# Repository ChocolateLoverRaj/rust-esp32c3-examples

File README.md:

# Programming ESP32-C3 with Rust
Examples with wiring diagrams for using some sensors with ESP32-C3, programmed with Rust

## Materials Needed
- ESP32-C3 (I bought [this one from AliExpress](https://www.aliexpress.us/item/3256805941172619.html), and I recommend buying it from "TENSTAR ROBOT")
- USB Cable to connect the ESP32-C3 to your computer. You can use a USB-A to USB-C cable or a USB-C to USB-C cable, they both work.
- Project-specific materials

## Try out the code
- Clone this repo
- Install Rust
- You may need to install some Rust stuff for ESP32-C3
- Plug in your ESP32-C3
- Make sure you have the permissions to access ESP32-C3 (`/dev/ttyACM0`)
- `cd` to the directory you want to run
- `cargo run`

## Supported Chips / Boards
This was originally only for the ESP32-C3, but it should be really easy to add support for other ESP32 chips / boards. Some examples already have support for the ESP32-S3 in addition to the C3, and there is one example for STM32, but it should be really easy to add support for other ESP32 chips / boards. Some examples already have support for the ESP32-S3 in addition to the C3, and there is one example for STM32. If you would like an example for a specific chip / board to be added, let me know. I have a ESP32-C3, ESP32-S3, and a stm32f103c8.

## `std` vs `no_std`
On ESP32 chips you can use Rust with `std` or `no_std`. Originally, every project in this repo used `std`. At some point I switched to using `no_std`. I don't recommend using `std` anymore. The old examples still use `std`. If you would like a `no_std` version of an example that is currently `std` only, let me know.

## On-demand Maintanance Mode
I want to maintain this repo to help people do stuff with their ESP32s. However, not all examples will be up to date. If there is an example that uses an out-of-date `esp-hal` version, is not working, or not working on your chip, or if you have a question, don't hesistate to create an issue. 

## Resources
This project is based off of these resources

### Rust on ESP32-C3
- [The Rust on ESP Book](https://docs.espressif.com/projects/rust/book/)
- [Embedded Rust (no_std) on Espressif](https://docs.espressif.com/projects/rust/no_std-training/)
- https://github.com/ivmarkov/rust-esp32-std-demo
- https://github.com/shanemmattner/ESP32-C3_Rust_Tutorials

### Project-specific resources
Can be found in the `README.md` files in folders

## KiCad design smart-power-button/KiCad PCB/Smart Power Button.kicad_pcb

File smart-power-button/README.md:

# Smart Power Button for Desktop Computers
## Why
- I got a gaming computer that I will also remotely use for programming
    - I want to play Overwatch
    - I want to do CPU heavy coding stuff like compiling the Linux kernel from source and working on large Rust projects
    - My Xbox (Xbox One S) can't run Overwatch well
    - My laptop (jinlon (HP Elite c1030 Chromebook)), can't compile code fast
- I want to remotely wake up my computer for programming
    - My gaming computer is connected to the living room TV. It does not have a good spot for programming.
- My computer can't Wake on LAN

## Features
- Remotely press the power and reset buttons of your computer, even when it's shut down or in suspend mode.
- Remotely view the status of the power LED and HDD LED, so you know if it's on / in suspend mode / off.
- Isolated circuits. The ESP32 does not need to have the same power source as the computer. For example, you can power it through USB-C that's connected to a laptop running on battery.
- Turn on the computer automatically when a Bluetooth game controller or other Bluetooth device is on and within range.

## Code setup
Copy `esp/example.env` to `esp/.env`. Edit the file to include your Wi-Fi info and GPIO pin numbers.

## Developing
### Making changes to the web page without flashing web page to ESP
Flashing all the web assets to the ESP takes a long time and wears down the flash more. Instead, do the following:
- In the `esp`, run `cargo r --no-default-features --features std,embassy,esp-idf-svc/native`. This will run without the `static-files` feature, which means that the files built by Trunk will not be included in the ESP code.
- View the output from the ESP to get the IP address of the ESP
- Copy `web/example.env` to `web/.env`. Edit the `WS_HOST` variable to be the ip address of the ESP
- Run `trunk serve` in `web`
- Open the web page served by Trunk in your browser instead of the ESP's server

### Running ESP in release mode to reduce size
Running the `esp` code in with `--release` reduces size, which saves time.

## Flashing Code for Normal Use
- Configure the `.env` files. See [#developing](#developing).
- Run `trunk serve --release` in `web`
- Run `cargo r --release` in `esp`

## Wiring Diagram

## Pictures of Breadboard

In my setup, I used an ATX power splitter so that I could access the 5VSB and GND pins to always power the ESP32-C3, even when the computer is off.

# PCB
To make the circuit compact and easier to use, I designed a PCB. I ordered the PCB with assembly on PCBWay, which sponsored the PCB prototyping for this project. As seen in the pictures, the quality of the PCB is great. The silkscreen is very clear including the QR Code in the bottom. The only issue is that some of the components were not perfectly aligned. I was stil able to plug in everything I needed to though. You can also order PCBs and PCBs with assembly for your own projects with [PCBWay](https://www.pcbway.com/).

I made a few mistakes in the PCB design:
- I used GPIO2, which is a special GPIO pin, which did not work as an input. To fix this, I cut off the connection to GPIO2 and soldered the trace to GPIO0 instead.
- The optocopulers for detecting the power and HDD LEDs assume that a 330Ω resistor is connected. This is okay if you get the wiring right, but while I was testing the PCB I accidentally destroyed 2 optocouplers (probably by connecting them to a 5V source without a resistor for a brief moment).
- The LEDs on the PCB and the extra external LEDs were supposed to work even when a ESP32-C3 Super-Mini was not attached, but it doesn't, since it needs a 3.3V source to work, which is only provided by the ESP32-C3 Super-Mini.
- I used resistors which will send 20mA (the maximum current) through the LEDs on the PCB, but this is ***way* too bright**! My PC is in my bedroom, and I had to disconnect it to fall asleep.

Here is the PCB in action:

[Here is the link to the original PCB just for reference](https://easyeda.com/editor#project_id=c5dba1f1b9a34bec985b2a5e179ea9b3) (it has the mistakes). I designed it on EasyEDA.

# Redesigned PCB
After I learned from my mistakes with the original design, I realized a few things:
- Always test the circuit as close as possible as you can test to the actual PCB before ordering the PCB
- The buttons and LEDs on the PCB are unnecessary
- The OLED display is unnecessary
- I do not need to order PCB assembly, I an use through hole components, order a PCB, and solder it myself.
- I should use KiCad instead of EasyEDA.

So I designed a new PCB with KiCad. It is located in the "KiCad PCB" folder. **I have not tested it yet.**

## Materials Needed
(In addition to a ESP32-C3)
- 6x PC817 (or other optocoupler). I bought [this one](https://www.aliexpress.us/item/3256806236608107.html)
- ATX Splitter (optional, for always powering the ESP32-C3 with the PSU). I bought [this one](https://www.aliexpress.us/item/3256805387697490.html?spm=a2g0o.order_list.order_list_main.38.36df1802MgpdVl&gatewayAdapt=glo2usa)
- Breadboard and wires or some way of connecting the components together

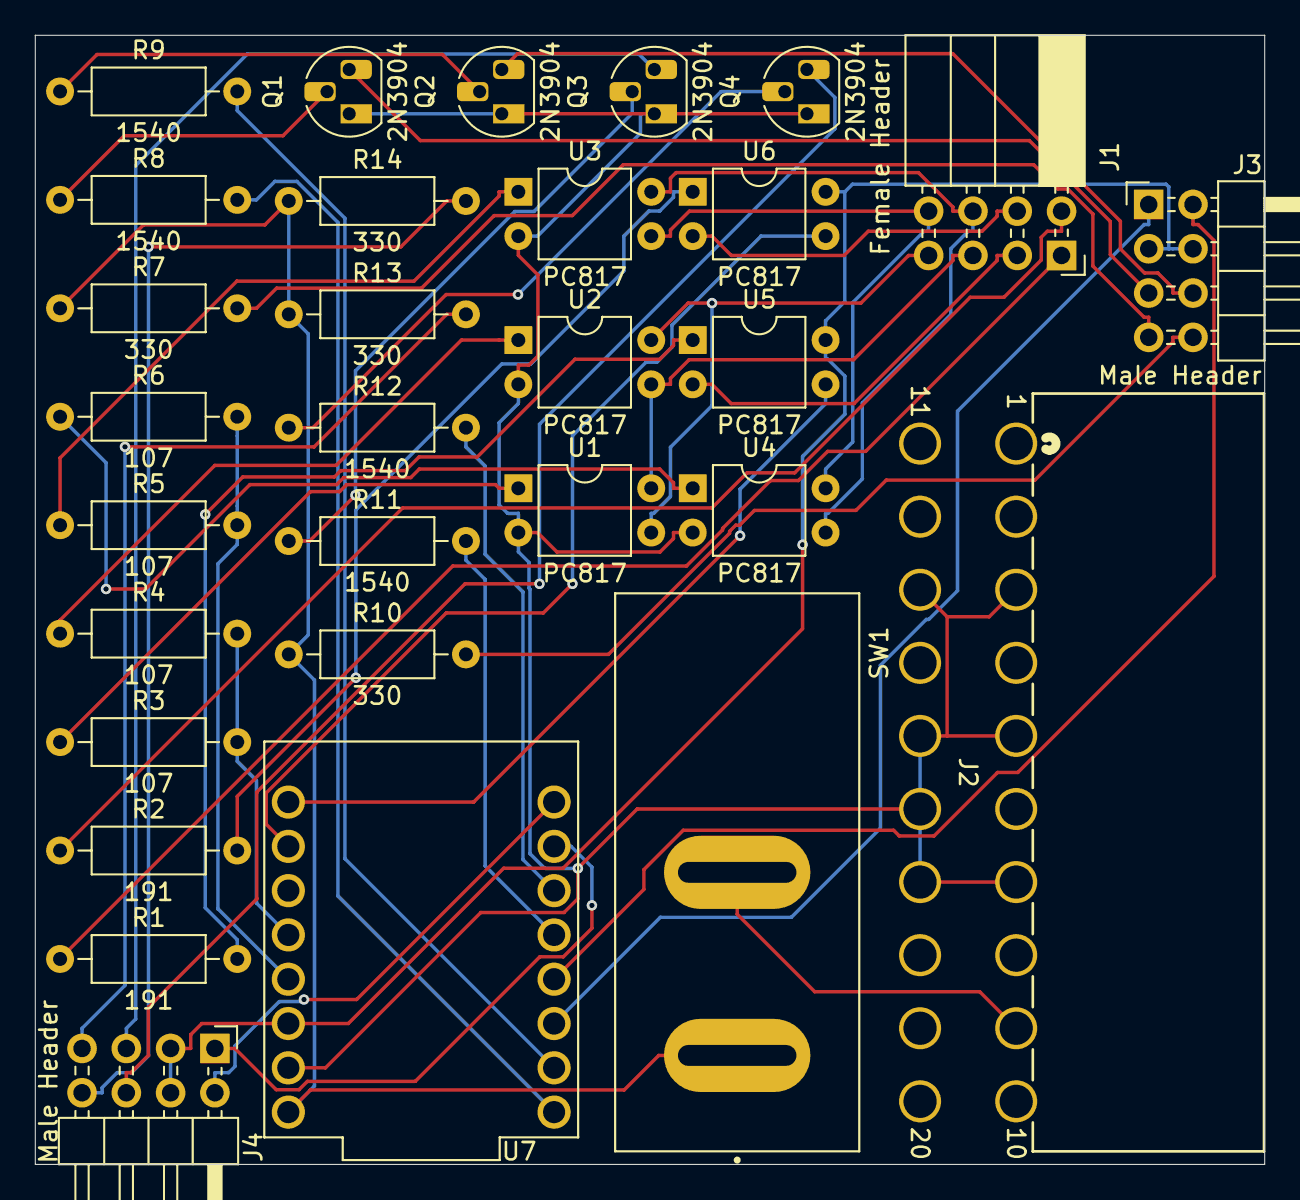
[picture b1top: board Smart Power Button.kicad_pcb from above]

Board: 2 copper layers, 70.5 x 64.8 mm, 30 parts (0 on the bottom side), 42 nets.

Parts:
J1: Female Header; PinSocket_2x04_P2.54mm_Horizontal
J2: 20-Pin ATX; CONN_2-1586041-0_TYCO
J3, J4: Male Header; PinHeader_2x04_P2.54mm_Horizontal
Q1, Q2, Q3, Q4: 2N3904; TO-92_HandSolder
R1, R2: 191; R_Axial_DIN0207_L6.3mm_D2.5mm_P10.16mm_Horizontal
R3, R4, R5, R6: 107; R_Axial_DIN0207_L6.3mm_D2.5mm_P10.16mm_Horizontal
R7, R10, R13, R14: 330; R_Axial_DIN0207_L6.3mm_D2.5mm_P10.16mm_Horizontal
R8, R9, R11, R12: 1540; R_Axial_DIN0207_L6.3mm_D2.5mm_P10.16mm_Horizontal
SW1: SW_SPST; SW_RB141C1100
U1, U2, U3, U4, U5, U6: PC817; DIP-4_W7.62mm
U7: ESP32-C3_SUPERMINI; MODULE_ESP32-C3_SUPERMINI

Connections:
+3.3V: J3.3, J3.4, J4.3, J4.4, U5.4, U6.4, U7.3.3 (3V3)
+5V: R7.1, R10.1, R13.1, R14.1, SW1.1 (A), U7.5V
GND: J2.3, J2.5, J2.7, J2.13, J2.15, J2.16, J2.17, Q1.1 (E), Q2.1 (E), Q3.1 (E), Q4.1 (E), U1.2, U2.2, U3.2, U4.2, U7.G (GND)
GPIO0: U5.3, U7.0 (GPIO0)
GPIO1: U6.3, U7.1 (GPIO1)
GPIO3: R3.2, R4.2, U7.3 (GPIO3)
GPIO4: R5.2, R6.2, U7.4 (GPIO4)
GPIO5: R8.2, U7.5 (GPIO5)
GPIO6: R9.2, U7.6 (GPIO6)
GPIO7: J3.1, U7.7 (GPIO7)
GPIO8: J3.2, U7.8 (GPIO8)
GPIO9: R11.2, U7.9 (GPIO9)
GPIO10: R12.2, U7.10 (GPIO10)
GPIO20: J4.1, U7.20 (GPIO20)
GPIO21: J4.2, U7.21 (GPIO21)
HDD LED+: J1.2, R2.1
HDD LED-: J1.4, U6.2
HDD SW 0: J1.6, U3.4, U4.3
HDD SW 1: J1.8, U3.3, U4.4
unnamed: J3.5, Q1.3 (C)
unnamed: J3.6, Q2.3 (C)
unnamed: J3.7, R7.2
unnamed: J3.8, R10.2
unnamed: J4.5, Q3.3 (C)
unnamed: J4.6, Q4.3 (C)
unnamed: J4.7, R13.2
unnamed: J4.8, R14.2
unnamed: Q1.2 (B), R8.1
unnamed: Q2.2 (B), R9.1
unnamed: Q3.2 (B), R11.1
unnamed: Q4.2 (B), R12.1
unnamed: R1.2, U5.1
unnamed: R2.2, U6.1
unnamed: R3.1, U1.1
unnamed: R4.1, U2.1
unnamed: R5.1, U3.1
unnamed: R6.1, U4.1
unnamed: J2.9, SW1.2 (B)
POWER SW 0: J1.5, U1.4, U2.3
POWER SW 1: J1.7, U1.3, U2.4
Power LED+: J1.1, R1.1
Power LED-: J1.3, U5.2

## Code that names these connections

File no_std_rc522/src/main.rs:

#![no_std]
#![no_main]

use defmt::{error, info, warn};
use embassy_executor::Spawner;
use embassy_time::{Delay, Duration, Instant, Timer};
use embedded_hal_bus::spi::ExclusiveDevice;
use esp_backtrace as _;
use esp_hal::{
    gpio::{Input, InputConfig, Level, Output, OutputConfig, Pull},
    interrupt::software::SoftwareInterruptControl,
    spi::{
        Mode,
        master::{Config, Spi},
    },
    time::Rate,
    timer::timg::TimerGroup,
};
use esp_println as _;
use futures::{
    future::{Either, select},
    pin_mut,
};
use mfrc522::{Mfrc522, RxGain, Uid, comm::blocking::spi::SpiInterface};

esp_bootloader_esp_idf::esp_app_desc!();

#[esp_rtos::main]
async fn main(spawner: Spawner) {
    let _ = spawner;

    let peripherals = esp_hal::init(Default::default());

    // Needed for esp_rtos
    let timg0 = TimerGroup::new(peripherals.TIMG0);
    let software_interrupt = SoftwareInterruptControl::new(peripherals.SW_INTERRUPT);
    esp_rtos::start(timg0.timer0, software_interrupt.software_interrupt0);

    // Reset the rc522 (optional, but good for when running new code without powering down the rc522)
    let mut reset_pin = Output::new(peripherals.GPIO10, Level::Low, OutputConfig::default());
    Timer::after(Duration::from_millis(10)).await;
    reset_pin.set_high();
    Timer::after(Duration::from_millis(5)).await;

    let mut led = Output::new(peripherals.GPIO8, Level::High, OutputConfig::default());

    let mut button = Input::new(
        peripherals.GPIO9,
        InputConfig::default().with_pull(Pull::Down),
    );

    let spi = Spi::new(
        peripherals.SPI2,
        Config::default()
            .with_frequency(Rate::from_mhz(10))
            .with_mode(Mode::_0),
    )
    .unwrap()
    .with_sck(peripherals.GPIO4)
    .with_mosi(peripherals.GPIO6)
    .with_miso(peripherals.GPIO5);

    let mut mfrc522 = Mfrc522::new(SpiInterface::new(
        ExclusiveDevice::new(
            spi,
            Output::new(peripherals.GPIO21, Level::High, OutputConfig::default()),
            Delay,
        )
        .unwrap(),
    ))
    .init()
    .unwrap();
    match mfrc522.version() {
        Ok(version) => info!("version 0x{:x}", version),
        Err(_e) => error!("version error"),
    }

    let rx_gains = [
        RxGain::DB18,
        RxGain::DB23,
        RxGain::DB33,
        RxGain::DB38,
        RxGain::DB43,
        RxGain::DB48,
    ];
    let mut rx_gain_index = 5;
    {
        let rx_gain = rx_gains[rx_gain_index];
        mfrc522.set_antenna_gain(rx_gain).unwrap();
        // info!("Initial rx gain: {rx_gain:?}");
    }

    let poll_interval = Duration::from_millis(20);
    // While a tag is present, its presence might not be continually read by the nfc reader
    // So we use a timeout before treating the tag as gone
    let tag_gone_timeout = poll_interval * 4;

    struct PreviousUid {
        uid: Uid,
        last_seen: Instant,
    }

    let mut previous_uid = None::<PreviousUid>;
    let mut uid_last_updated = Instant::now();
    loop {
        let now = Instant::now();
        let current_uid = if let Ok(atqa) = mfrc522.new_card_present() {
            match mfrc522.select(&atqa) {
                Ok(uid) => Some(uid),
                Err(_e) => {
                    warn!("Select error");
                    None
                }
            }
        } else {
            None
        };

        let previous_present_uid = previous_uid.as_ref().and_then(|previous_uid| {
            if uid_last_updated - previous_uid.last_seen < tag_gone_timeout {
                Some(&previous_uid.uid)
            } else {
                None
            }
        });
        let current_present_uid =
            current_uid
                .as_ref()
                .or(previous_uid.as_ref().and_then(|previous_uid| {
                    if now - previous_uid.last_seen < tag_gone_timeout {
                        Some(&previous_uid.uid)
                    } else {
                        None
                    }
                }));

        // If the present uid changed, update the display (LED and logging)
        if previous_present_uid.map(Uid::as_bytes) != current_present_uid.map(Uid::as_bytes) {
            info!("UID: {:?}", current_present_uid);
            led.set_level(current_present_uid.is_none().into());
        }

        // Update the state
        if let Some(uid) = current_uid {
            previous_uid = Some(PreviousUid {
                uid,
                last_seen: now,
            });
        }
        uid_last_updated = now;

        let button_fut = button.wait_for_rising_edge();
        pin_mut!(button_fut);
        match select(button_fut, Timer::after(poll_interval)).await {
            Either::Left(_) => {
                rx_gain_index += 1;
                if rx_gain_index == rx_gains.len() {
                    rx_gain_index = 0;
                }
                {
                    let rx_gain = rx_gains[rx_gain_index];
                    mfrc522.set_antenna_gain(rx_gain).unwrap();
                    info!("Set rx gain to ");
                }
            }
            Either::Right(_) => {}
        }
    }
}

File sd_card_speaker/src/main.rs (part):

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    let spi_bus = Mutex::<CriticalSectionRawMutex, _>::new(
        Spi::new(peripherals.SPI2, Config::default())
            .unwrap()
            .with_sck(peripherals.GPIO4)
            .with_mosi(peripherals.GPIO3)
            .with_miso(peripherals.GPIO2)
            .with_dma(peripherals.DMA_CH0)
            .with_buffers(dma_rx_buf, dma_tx_buf)
            .into_async(),
    );

    let cs = Output::new(peripherals.GPIO1, Level::High, OutputConfig::default());

    let mut sd_card = SpiSdCard::new(
        EmbassySharedSpiBus::new(&spi_bus),
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    let tx_buffer = tx_buffer;
    let tx = i2s
        .i2s_tx
        .with_bclk(peripherals.GPIO10)
        .with_dout(peripherals.GPIO20)
        .with_ws(peripherals.GPIO21)
        .build(tx_descriptors);
    let mut transfer = tx.write_dma_circular_async(tx_buffer).unwrap();

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
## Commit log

2024-01-04 Upload code
2024-01-04 More documentation
2024-01-04 Better readme
2024-01-05 Analog Fritzing sketch
2024-01-05 Update READMEs
2024-01-06 Add VL53L0X example
2024-01-06 Use interrupts with GPIO1
2024-01-07 HC-SR04
2024-01-07 Web Serial
2024-01-07 Title
2024-01-07 Add demo link
2024-01-07 USB Echo
2024-01-07 Web serial send input
2024-01-07 Disable watchdog in echo example
2024-01-07 Better scrolling to bottom
2024-01-08 Disable watchdog timer for usb-echo
2024-01-08 nvs-led
2024-01-08 Start external led control
2024-01-08 Turn LED on or off using "on" or "off" commands
2024-01-08 Also toggle led with button
2024-01-09 Example with 3 ways of changing LED state
2024-01-10 Update BLE in example
2024-01-11 Color output in web page
2024-01-11 Use npm package
2024-01-20 Convert digital to async
2024-01-20 Sensor connect
2024-01-20 Randomly generated name that gets persisted
2024-01-20 Info from Cargo.toml in BLE characteristics
2024-01-21 Change name and passkey
2024-01-22 Get and set name and passkey
2024-01-22 Refactor receiver loops
2024-01-23 Get/set passkey from USB
2024-01-23 Split things into multiple files
2024-01-25 Try calling `set_short_name` directly instead of using channels
2024-01-26 Remove short name channel
2024-01-26 Switch from channels to arc and mutex
2024-01-27 Separate file for short name characteristic
2024-01-28 Notify changes to name through USB
2024-01-28 Move passkey characteristic to new file
    Also notify USB of changes to passkey
2024-01-29 Turn BLE on or off
2024-02-07 Read from ir sensor and subscribe using interrupts
2024-02-10 Distance sensor
2024-02-11 Better ir sensor
    Detects if ir led is connected
    Only activates emitter when receiver is being used
2024-02-11 Get capabilities from USB
    BLE can get capabilities by seeing which characteristics are part of the service
2024-02-11 Check if already subscribed
2024-02-11 Detect LED
2024-02-11 Create web app
2024-02-17 Progress with sensor connect web
2024-02-17 Use Leptos instead of wasm-react
2024-02-17 Add netlify config for sensor connect web
2024-02-17 Run npm i
2024-02-17 install without production env
2024-02-17 Use rust nightly
2024-02-17 Link to live website
2024-02-18 Get device name
2024-02-19 Get name usb
2024-02-24 View and change name
2024-02-25 Characteristic trait
2024-02-25 Remove unnecessary clone
2024-04-02 BACKUP
2024-04-02 Add `Cargo.lock` to files managed by git
    This makes sure that new downlaods will have consistent builds.
2024-04-02 Update to make it work in NixOS
2024-04-02 Add nix shell for web
2024-04-19 Passkey characteristic
2024-04-19 BLE on component
2024-04-25 Flake ldproxy
2024-05-01 Ir and distance sensor info in web page
    Currently annoying cuz there's a bub with subscribing and unsubscribing to the IR and distance characteristics on the esp32c3 side.
2024-05-03 ir and distance sensor for BLE connection
    Doesn't work properly for USB connection, maybe won't be fixed for a while
2024-05-27 Adjust gpio pins
2024-06-08 FHS Flake
2024-06-30 Smart power button
2024-06-30 More configurable with env vars
2024-06-30 Better why
2024-07-04 Fix web code when WS_HOST is `None`
2024-07-04 Swap on/off for input and output pins
2024-07-05 Use WSS for HTTPS
2024-07-05 Replace string_to_error.rs with anyhow
2024-07-21 Wakeup on Bluetooth device
2024-07-26 TV control and wakeup reason
2024-07-27 Smart power button pictures and diagram
2024-07-28 IR Remote docs
2024-08-07 Sound system works
2024-08-07 Startup flash, and fixes
2024-08-11 Consistent TV on/off
    Well, it's pretty consistent. Not 100% though.
2024-08-11 TV managing done
2024-08-11 Make `esp` and `web` buildable
2024-08-13 Do not restart NetworkManager when program is exiting
2024-08-13 More delay, don't ignore TV state
2024-08-13 Replace join! with try_join!
2024-09-12 OLED Display
2024-09-13 Update mac address
2024-10-13 KiCad PCB for smart power button
2024-10-13 Format watch_input.rs
2024-10-13 Add OLED display to smart power button
2024-10-13 max7219
2024-10-13 PCB writing
2024-11-03 Update flake and cleanup some code
2025-11-29 Use rc522 with std
2025-11-30 Nicely working
2025-11-30 Fritzing for RC522 example
2025-12-01 MicroSD example
2025-12-06 unwrap of `self.time_driver.as_mut()` failed: NoneError
2025-12-06 Fixed it!
2025-12-06 Toggly
2025-12-06 Simplify
2025-12-06 Try to use BLE (not working)
2025-12-16 Add hello world example
2025-12-16 Add WS2812 example
    I will probably make all examples no_std and even convert the std ones to no_std in the future
2025-12-18 Works!
2025-12-20 SD card!
2025-12-20 SD card plug and unplug detection
    (Through polling)
2025-12-20 Reduce SPI speed for SD card
2025-12-21 Start Async SD Card
2025-12-21 Command 58
2025-12-21 Finished SPI intiialization flow
2025-12-21 Get CSD
2025-12-21 Get card capacity
2025-12-21 Handle R1 = 0x0 for CMD0
2025-12-21 Make some changes
2025-12-21 More changes
2025-12-21 Fix voltage accepted bug
2025-12-21 Bring back dummy 0xFF to CMD0
2025-12-21 Back to stricter CMD8
2025-12-21 Reduce code size
2025-12-21 Reference library instead of module
2025-12-21 Upgrade to 25 Mhz
2025-12-21 Retry CMD0
2025-12-21 Turn on CRC
2025-12-21 Get CID
2025-12-21 Check SD card presendce
2025-12-22 Read data and kind of benchmark
2025-12-22 Read multiple for benchmark
2025-12-22 Use DMA to achieve almost 2x speed
2025-12-24 Read root dir
2025-12-26 7.64 Mbit/s !
2025-12-26 Investigate it not working on SanDisk SD cards
2025-12-26 Try to get it working on the SanDisk 128 GB
2025-12-27 Nicely read root dir
2025-12-27 Clean up
2025-12-28 Start SD Card + Speaker example
2025-12-30 Play from SD card!
2025-12-31 Increase DMA buffer size
2025-12-31 Unwrap available() result to detect DMA late errors
2025-12-31 Cleaup code
2025-12-31 Remove tests / benchmarks
2025-12-31 Differentiate volume label and file
2026-01-01 Handle hot plug and unplug of SD cards
2026-01-03 STM32 PWM
2026-01-03 Custom rotary encoder logic
2026-01-03 Control LED brightness with rotary encoder
2026-01-04 Rotary encoder Fritzing sketch
2026-01-06 1 Mbit/s UART connection between two esp32c3's without DMA
2026-01-07 Use DMA for UART
2026-01-07 track missed bytes when receiving
2026-01-07 Bring back uart link with async without DMA
    This one works with no bytes lost at 1 Mbit/s, which is better than with
    DMA
2026-01-07 Call test fn
2026-01-07 Start using DMA circular read
2026-01-07 Mostly working almost 4Mbit/s data transfer with UART using DMA
2026-01-08 Found out why checking for missed bytes reduces throughput
    The code to check for missed bytes takes so long that the transmitting
    loop gets blocked for too long and does not send at the full 5Mbps.
2026-01-08 Working 4 Mbit/s UART with DMA!
2026-01-08 Use helper buffer macros
2026-01-09 Use println feature in esp-backtrace for no_std_hello_world
2026-01-09 Edit OLED display
2026-01-09 WS2812 SPI and UART examples
2026-01-09 Add ws2812_rmt example
2026-01-23 Add Mcp23017 example
2026-01-29 Update gpio expander code
2026-01-29 8x8 rgb led matrix
2026-01-29 Improve
2026-03-14 Working xbox controller input!
2026-03-14 Format Cargo.toml
2026-03-14 RUMBLE WORKS
2026-03-14 Proper characteristic discovery
2026-03-14 Rumble based on button presses
2026-03-22 Add esp32s3
2026-03-25 Make some examples more `main` ready
2026-03-25 Update recommended board
2026-05-05 Update hello world and make it support esp32s3
2026-05-09 Update README and commit changes
2026-05-11 Push dev
2026-05-13 Fast transfers
2026-05-14 ALMOST 17 Mbps transfer rate!
2026-05-14 Use dedicated SPI pins
2026-05-14 Add retry logic
2026-05-17 Try making easier init
